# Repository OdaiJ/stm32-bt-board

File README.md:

# STM32 Bluetooth Demo Board

## Overview

A demo board I made as a project to learn PCB design fundamentals. The board is missing
some key features that make it general purpose; like headers for the unused MCU pins, however, it was a fun little project that took me a few months :)

This board was designed according to Phil's Lab's amazing videos on YouTube.

Click here to view it on 

## Todos

1. More careful choice of components for BOM; as the MOQ is too high for most components as of now.

## Notes

Assembly PDFs are broken - KiCad won't export them correctly for some reason.

Also, as of now, I had to manually edit the CPL file so JLCPCB doesn't cry about it. P.S.: I do NOT recommend using the the JLCPCB Fabrication Tool KiCad plugin; because it didn't work for me - but that was probably my fault though.

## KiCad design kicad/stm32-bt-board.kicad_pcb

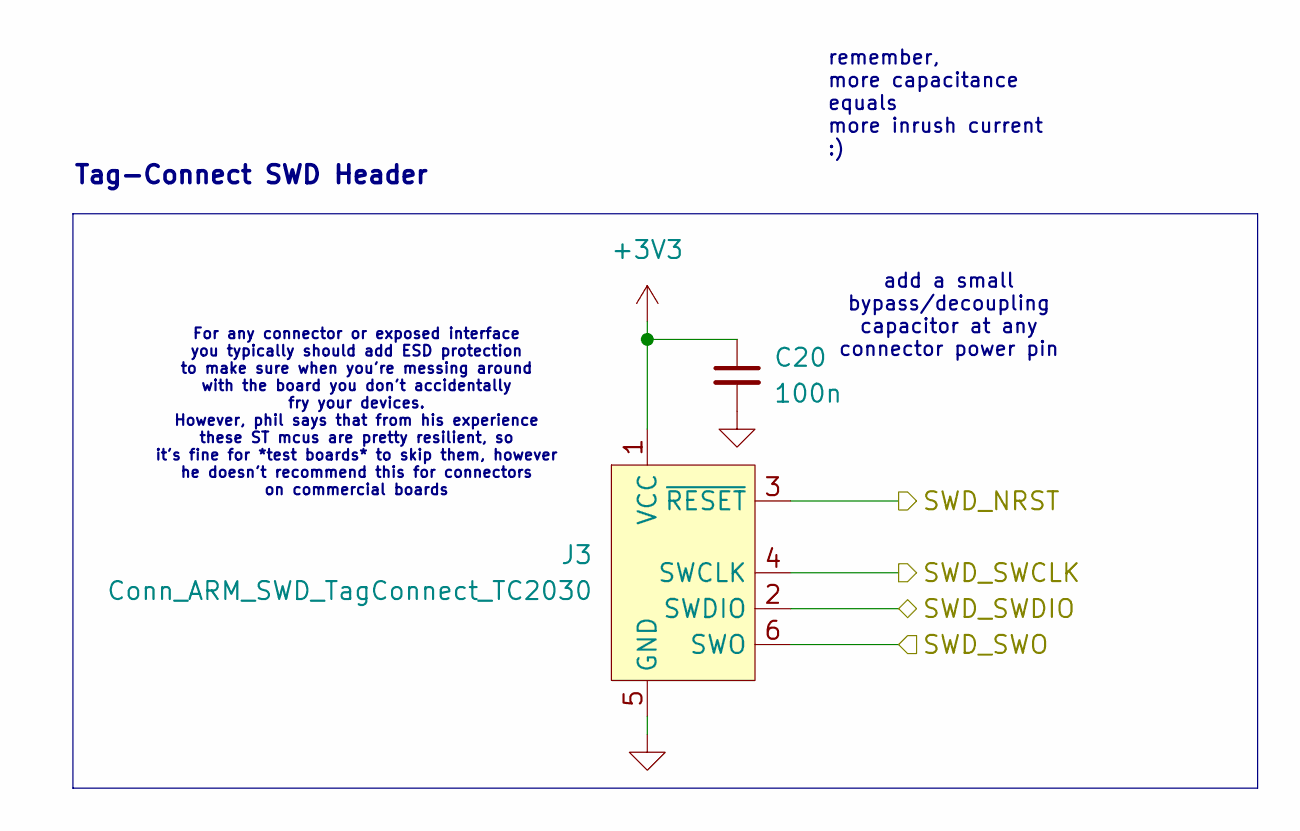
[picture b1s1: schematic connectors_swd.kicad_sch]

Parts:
C20: 100n; C_0402_1005Metric; MPN CC0402KRX7R7BB104
J3: Conn_ARM_SWD_TagConnect_TC2030; Tag-Connect_TC2030-IDC-FP_2x03_P1.27mm_Vertical

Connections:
+3V3: C20.1, J3.1 (VCC); also elsewhere on the board
/SWD_SWCLK: J3.4 (SWCLK); also elsewhere on the board
/SWD_SWDIO: J3.2 (SWDIO); also elsewhere on the board
/SWD_SWO: J3.6 (SWO); also elsewhere on the board
GND: C20.2, J3.5 (GND); also elsewhere on the board
NRST_IN: J3.3 (~RESET); also elsewhere on the board

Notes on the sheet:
remember, more capacitance equals more inrush current :)
For any connector or exposed interface you typically should add ESD protection to make sure when you're messing around with the board you don't accidentally fry your devices. However, phil says that from his experience these ST mcus are pretty resilient, so it's fine for *test boards* to skip them,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
Tag-Connect SWD Header
add a small bypass/decoupling capacitor at any connector power pin

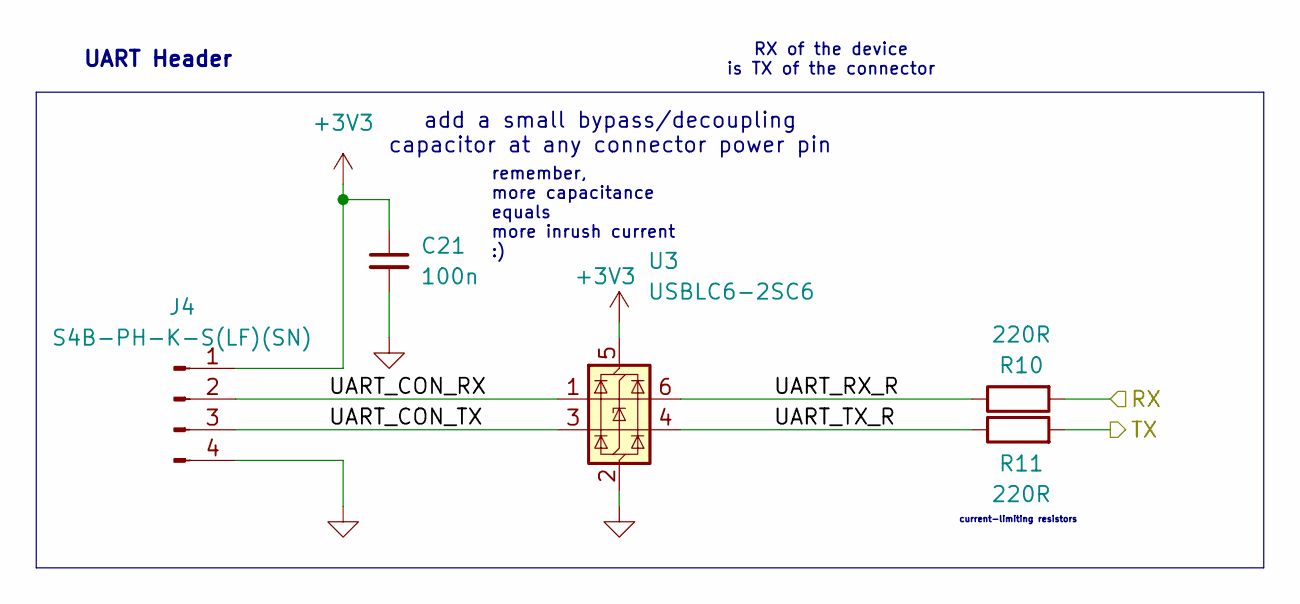
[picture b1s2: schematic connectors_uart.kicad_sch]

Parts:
C21: 100n; C_0402_1005Metric; MPN CC0402KRX7R7BB104
J4: S4B-PH-K-S(LF)(SN); MPN S4B-PH-K-S(LF)(SN)
R10, R11: 220R; R_0402_1005Metric; MPN FRC0402F2200TS
U3: USBLC6-2SC6; SOT-23-6; MPN USBLC6-2SC6

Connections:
+3V3: C21.1, J4.1, U3.5 (VBUS); also elsewhere on the board
/Connectors/UART/UART_CON_RX: J4.2, U3.1 (I/O1)
/Connectors/UART/UART_CON_TX: J4.3, U3.3 (I/O2)
/Connectors/UART/UART_RX_R: R10.1, U3.6 (I/O1)
/Connectors/UART/UART_TX_R: R11.1, U3.4 (I/O2)
/UART_MCU_RX: R11.2; also elsewhere on the board
/UART_MCU_TX: R10.2; also elsewhere on the board
GND: C21.2, J4.4, U3.2 (GND); also elsewhere on the board

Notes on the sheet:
remember, more capacitance equals more inrush current :)
add a small bypass/decoupling capacitor at any connector power pin
UART Header
RX of the device is TX of the connector
current-limiting resistors

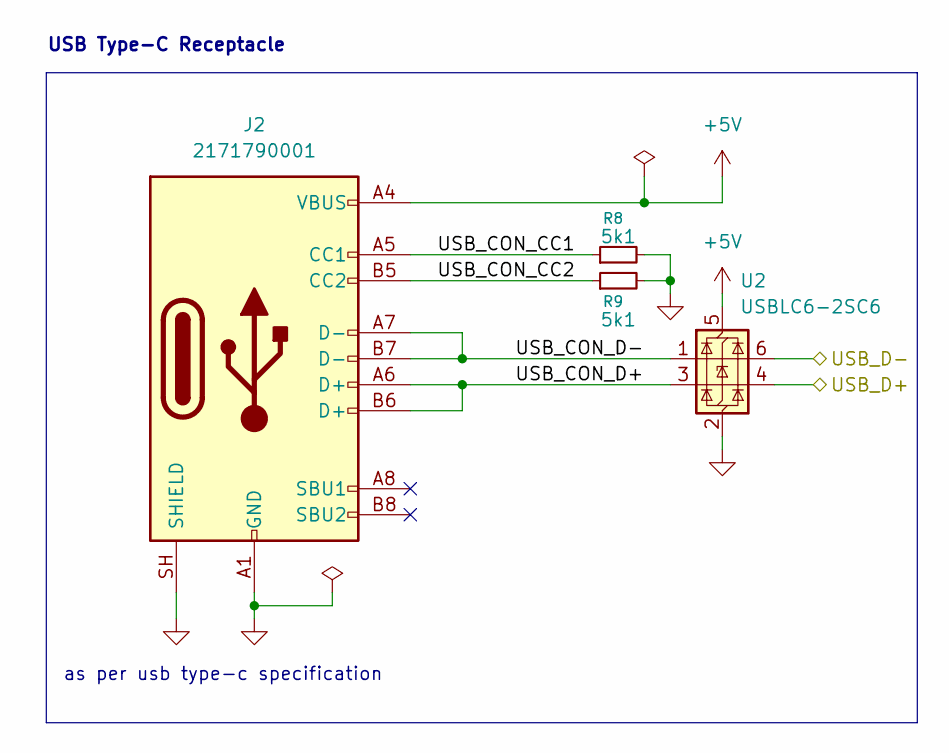
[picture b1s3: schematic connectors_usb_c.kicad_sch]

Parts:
J2: 2171790001; MPN 2171790001
R8, R9: 5k1; R_0402_1005Metric; MPN RC0402FR-075K1L
U2: USBLC6-2SC6; SOT-23-6; MPN USBLC6-2SC6

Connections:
+5V: J2.A4 (VBUS), J2.A9 (VBUS), J2.B4 (VBUS), J2.B9 (VBUS), U2.5 (VBUS); also elsewhere on the board
/Connectors/USB Type C/USB_CON_CC1: J2.A5 (CC1), R8.1
/Connectors/USB Type C/USB_CON_CC2: J2.B5 (CC2), R9.1
/Connectors/USB Type C/USB_CON_D+: J2.A6 (D+), J2.B6 (D+), U2.3 (I/O2)
/Connectors/USB Type C/USB_CON_D-: J2.A7 (D-), J2.B7 (D-), U2.1 (I/O1)
/USB_D+: U2.4 (I/O2); also elsewhere on the board
/USB_D-: U2.6 (I/O1); also elsewhere on the board
GND: J2.A1 (GND), J2.A12 (GND), J2.B1 (GND), J2.B12 (GND), J2.SH (SHIELD), R8.2, R9.2, U2.2 (GND); also elsewhere on the board

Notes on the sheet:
USB Type-C Receptacle
as per usb type-c specification

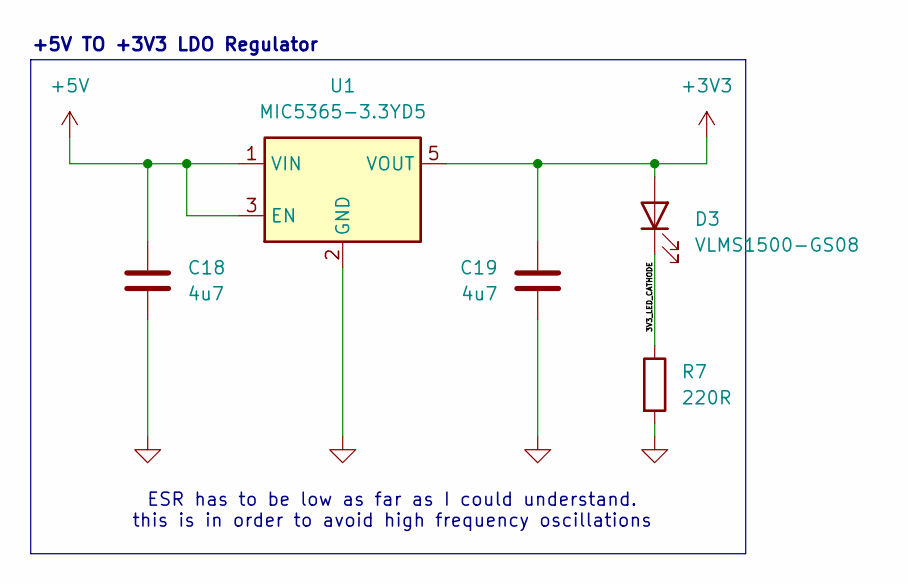
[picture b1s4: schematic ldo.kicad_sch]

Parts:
C18, C19: 4u7; C_0603_1608Metric; MPN CL10A475KL8NRNC
D3: VLMS1500-GS08; LED_0402_1005Metric; MPN VLMS1500-GS08
R7: 220R; R_0402_1005Metric; MPN FRC0402F2200TS
U1: MIC5365-3.3YD5; TSOT-23-5; MPN MIC5365-3.3YD5-TR

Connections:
+3V3: C19.1, D3.2 (A), U1.5 (VOUT); also elsewhere on the board
+5V: C18.1, U1.1 (VIN), U1.3 (EN); also elsewhere on the board
/LDO/3V3_LED_CATHODE: D3.1 (K), R7.1
GND: C18.2, C19.2, R7.2, U1.2 (GND); also elsewhere on the board

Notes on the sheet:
+5V TO +3V3 LDO Regulator
ESR has to be low as far as I could understand. this is in order to avoid high frequency oscillations

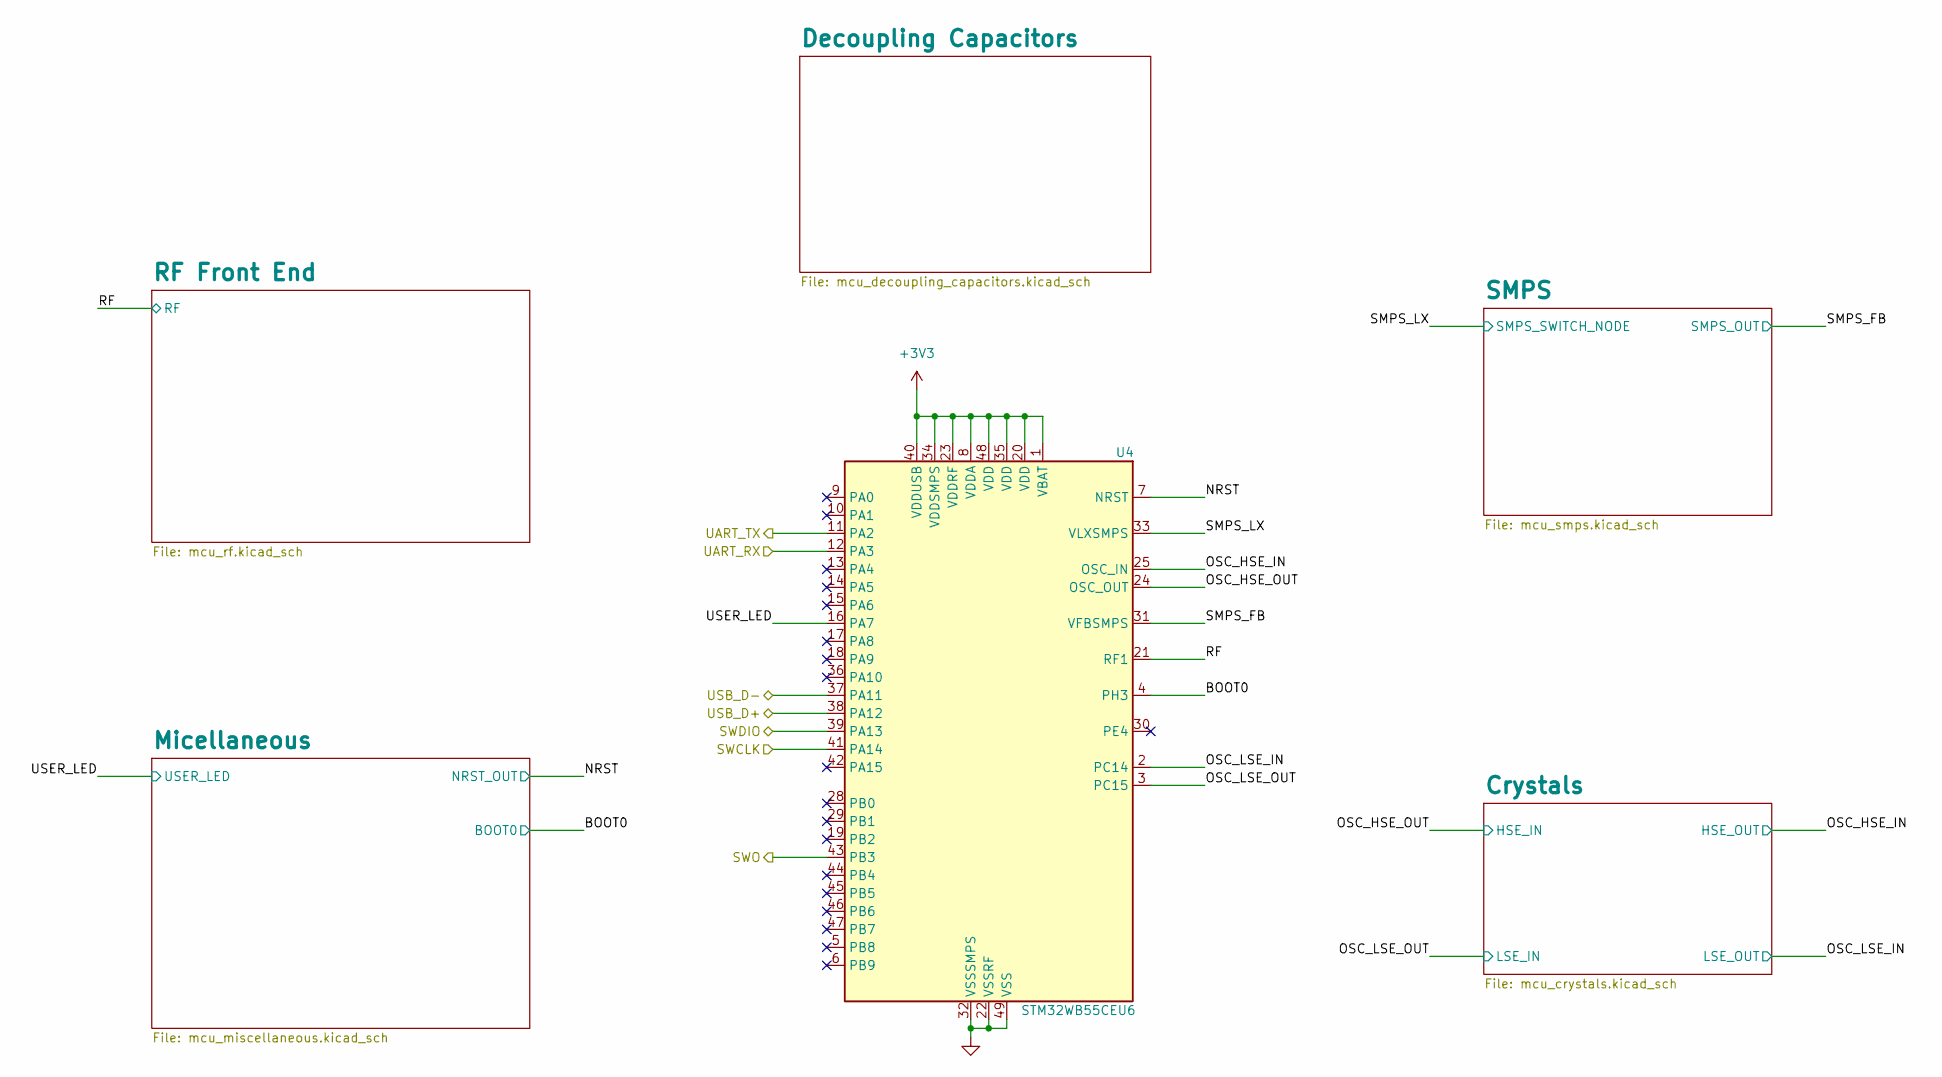
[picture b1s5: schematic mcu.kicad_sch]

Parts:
U4: STM32WB55CEU6; QFN-48-1EP_7x7mm_P0.5mm_EP5.6x5.6mm; MPN STM32WB55CEU6

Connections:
+3V3: U4.1 (VBAT), U4.8 (VDDA), U4.20 (VDD), U4.23 (VDDRF), U4.34 (VDDSMPS), U4.35 (VDD), U4.40 (VDDUSB), U4.48 (VDD); also elsewhere on the board
/Microcontroller/BOOT0: U4.4 (PH3); also elsewhere on the board
/Microcontroller/NRST: U4.7 (NRST); also elsewhere on the board
/Microcontroller/OSC_HSE_IN: U4.25 (OSC_IN); also elsewhere on the board
/Microcontroller/OSC_HSE_OUT: U4.24 (OSC_OUT); also elsewhere on the board
/Microcontroller/OSC_LSE_IN: U4.2 (PC14); also elsewhere on the board
/Microcontroller/OSC_LSE_OUT: U4.3 (PC15); also elsewhere on the board
/Microcontroller/RF: U4.21 (RF1); also elsewhere on the board
/Microcontroller/SMPS_FB: U4.31 (VFBSMPS); also elsewhere on the board
/Microcontroller/SMPS_LX: U4.33 (VLXSMPS); also elsewhere on the board
/Microcontroller/USER_LED: U4.16 (PA7); also elsewhere on the board
/SWD_SWCLK: U4.41 (PA14); also elsewhere on the board
/SWD_SWDIO: U4.39 (PA13); also elsewhere on the board
/SWD_SWO: U4.43 (PB3); also elsewhere on the board
/UART_MCU_RX: U4.12 (PA3); also elsewhere on the board
/UART_MCU_TX: U4.11 (PA2); also elsewhere on the board
/USB_D+: U4.38 (PA12); also elsewhere on the board
/USB_D-: U4.37 (PA11); also elsewhere on the board
GND: U4.22 (VSSRF), U4.32 (VSSSMPS), U4.49 (VSS); also elsewhere on the board

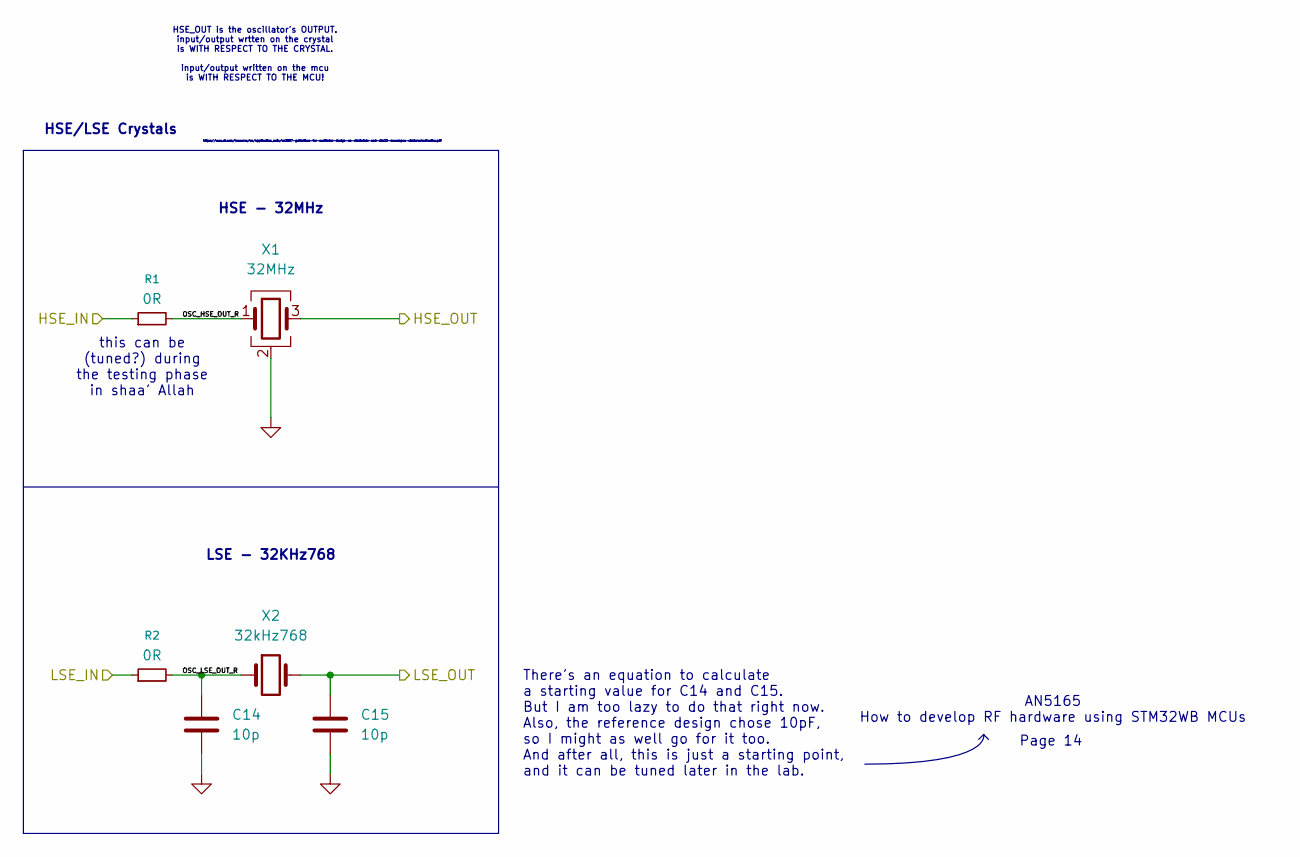
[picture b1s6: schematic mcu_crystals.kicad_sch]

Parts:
C14, C15: 10p; C_0402_1005Metric; MPN GRM1555C1H100FA01D
R1, R2: 0R; R_0402_1005Metric; MPN CRCW04020000Z0ED
X1: 32MHz; Crystal_SMD_2016-4Pin_2.0x1.6mm; MPN NX2016SA-32MHZ-EXS00A-CS06654
X2: 32kHz768; Crystal_SMD_2012-2Pin_2.0x1.2mm; MPN NX2012SA-32.768KHZ-STD-MUB-2

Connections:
/Microcontroller/Crystals/OSC_HSE_OUT_R: R1.2, X1.1
/Microcontroller/Crystals/OSC_LSE_OUT_R: C14.1, R2.2, X2.1
/Microcontroller/OSC_HSE_IN: X1.3; also elsewhere on the board
/Microcontroller/OSC_HSE_OUT: R1.1; also elsewhere on the board
/Microcontroller/OSC_LSE_IN: C15.1, X2.2; also elsewhere on the board
/Microcontroller/OSC_LSE_OUT: R2.1; also elsewhere on the board
GND: C14.2, C15.2, X1.2 (G), X1.4 (G); also elsewhere on the board

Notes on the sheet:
HSE/LSE Crystals
HSE - 32MHz
https://www.st.com/resource/en/application_note/an2867-guidelines-for-oscillator-design-on-stm8afals-and-stm32-mcusmpus-stmicroelectronics.pdf
LSE - 32KHz768
Page 14
AN5165 How to develop RF hardware using STM32WB MCUs
There's an equation to calculate a starting value for C14 and C15. But I am too lazy to do that right now. Also, the reference design chose 10pF, so I might as well go for it too. And after all, this is just a starting point, and it can be tuned later in the lab.
this can be (tuned?) during the testing phase in shaa' Allah
HSE_OUT is the oscillator's OUTPUT. input/output wrtten on the crystal is WITH RESPECT TO THE CRYSTAL. input/output written on the mcu is WITH RESPECT TO THE MCU!

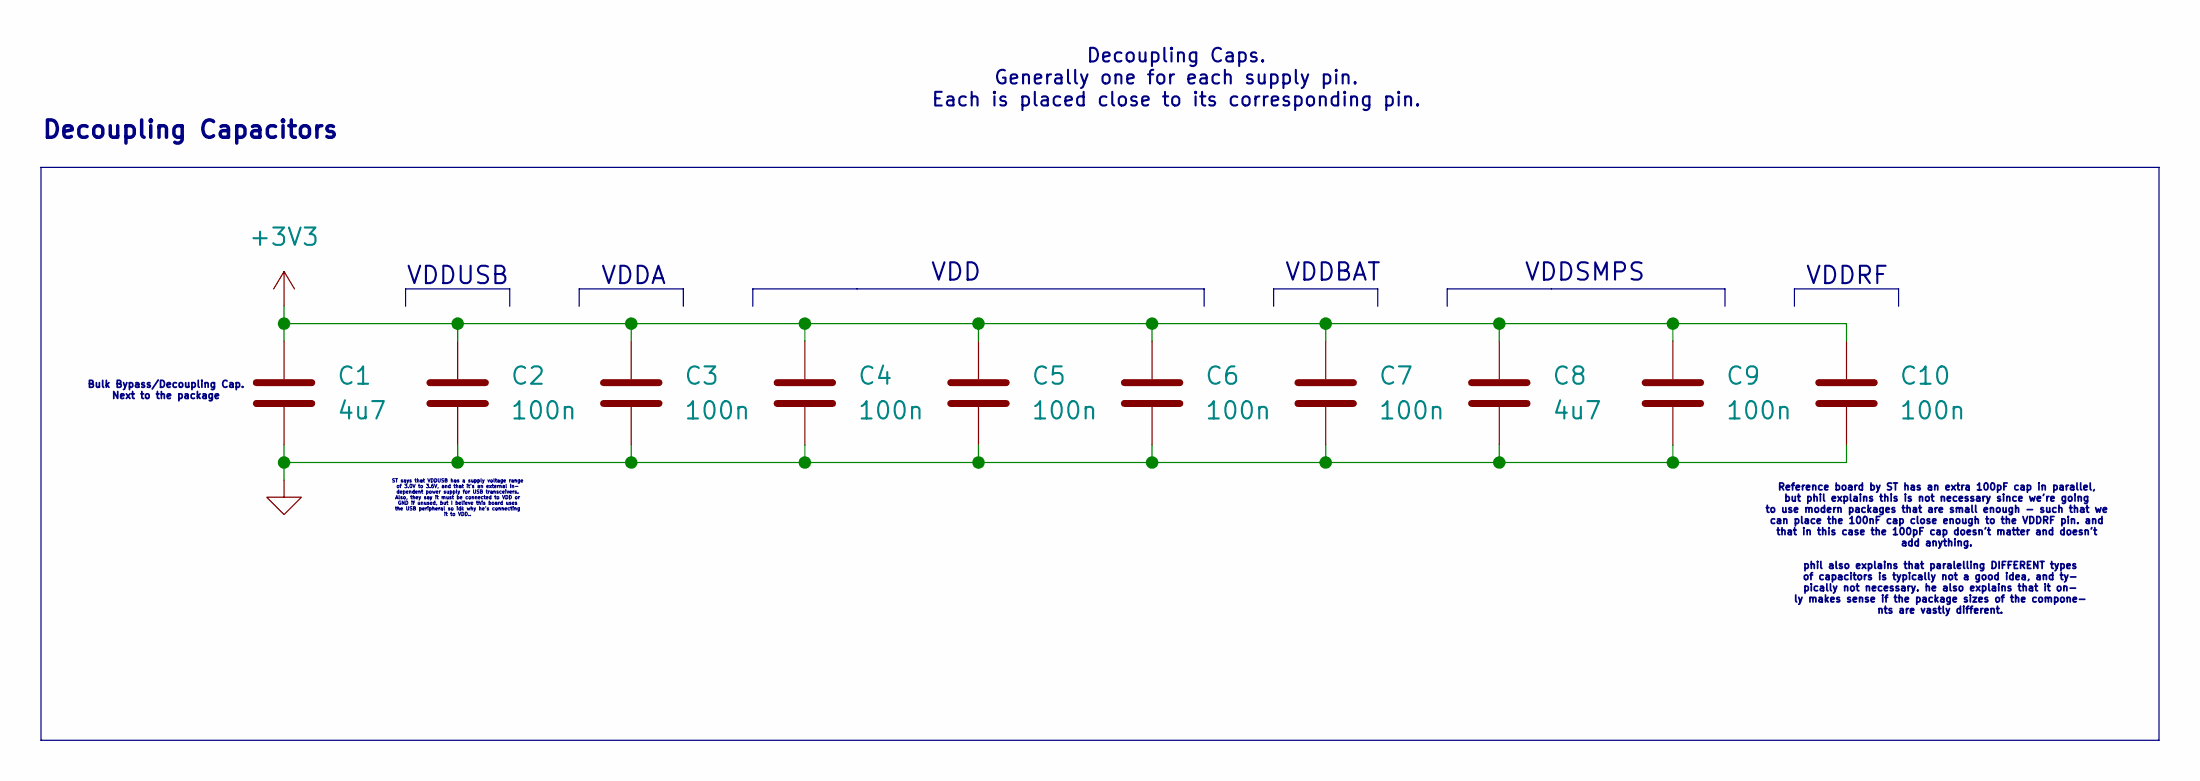
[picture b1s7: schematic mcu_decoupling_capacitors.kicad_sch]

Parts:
C1, C8: 4u7; C_0603_1608Metric; MPN CL10A475KL8NRNC
C2, C3, C4, C5, C6, C7, C9, C10: 100n; C_0402_1005Metric; MPN CC0402KRX7R7BB104

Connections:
+3V3: C1.1, C2.1, C3.1, C4.1, C5.1, C6.1, C7.1, C8.1, C9.1, C10.1; also elsewhere on the board
GND: C1.2, C2.2, C3.2, C4.2, C5.2, C6.2, C7.2, C8.2, C9.2, C10.2; also elsewhere on the board

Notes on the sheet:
VDDRF
VDD
Decoupling Caps. Generally one for each supply pin. Each is placed close to its corresponding pin.
Reference board by ST has an extra 100pF cap in parallel, but phil explains this is not necessary since we're going to use modern packages that are small enough - such that we can place the 100nF cap close enough to the VDDRF pin. and that in this case the 100pF cap doesn't matter and doesn't add a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
phil also explains that paralelling DIFFERENT types of capacitors is typically not a good idea, and ty- pically not necessary. he also explains that it on- ly makes sense if the package sizes of the compone- nts are vastly different.
Bulk Bypass/Decoupling Cap. Next to the package
Decoupling Capacitors
VDDBAT
VDDUSB
VDDA
ST says that VDDUSB has a supply voltage range of 3.0V to 3.6V, and that it's an external in- dependent power supply for USB transceivers. Also, they say it must be connected to VDD or GND if unused, but I believe this board uses the USB peripheral so idk why he's connecting it to VDD..
VDDSMPS

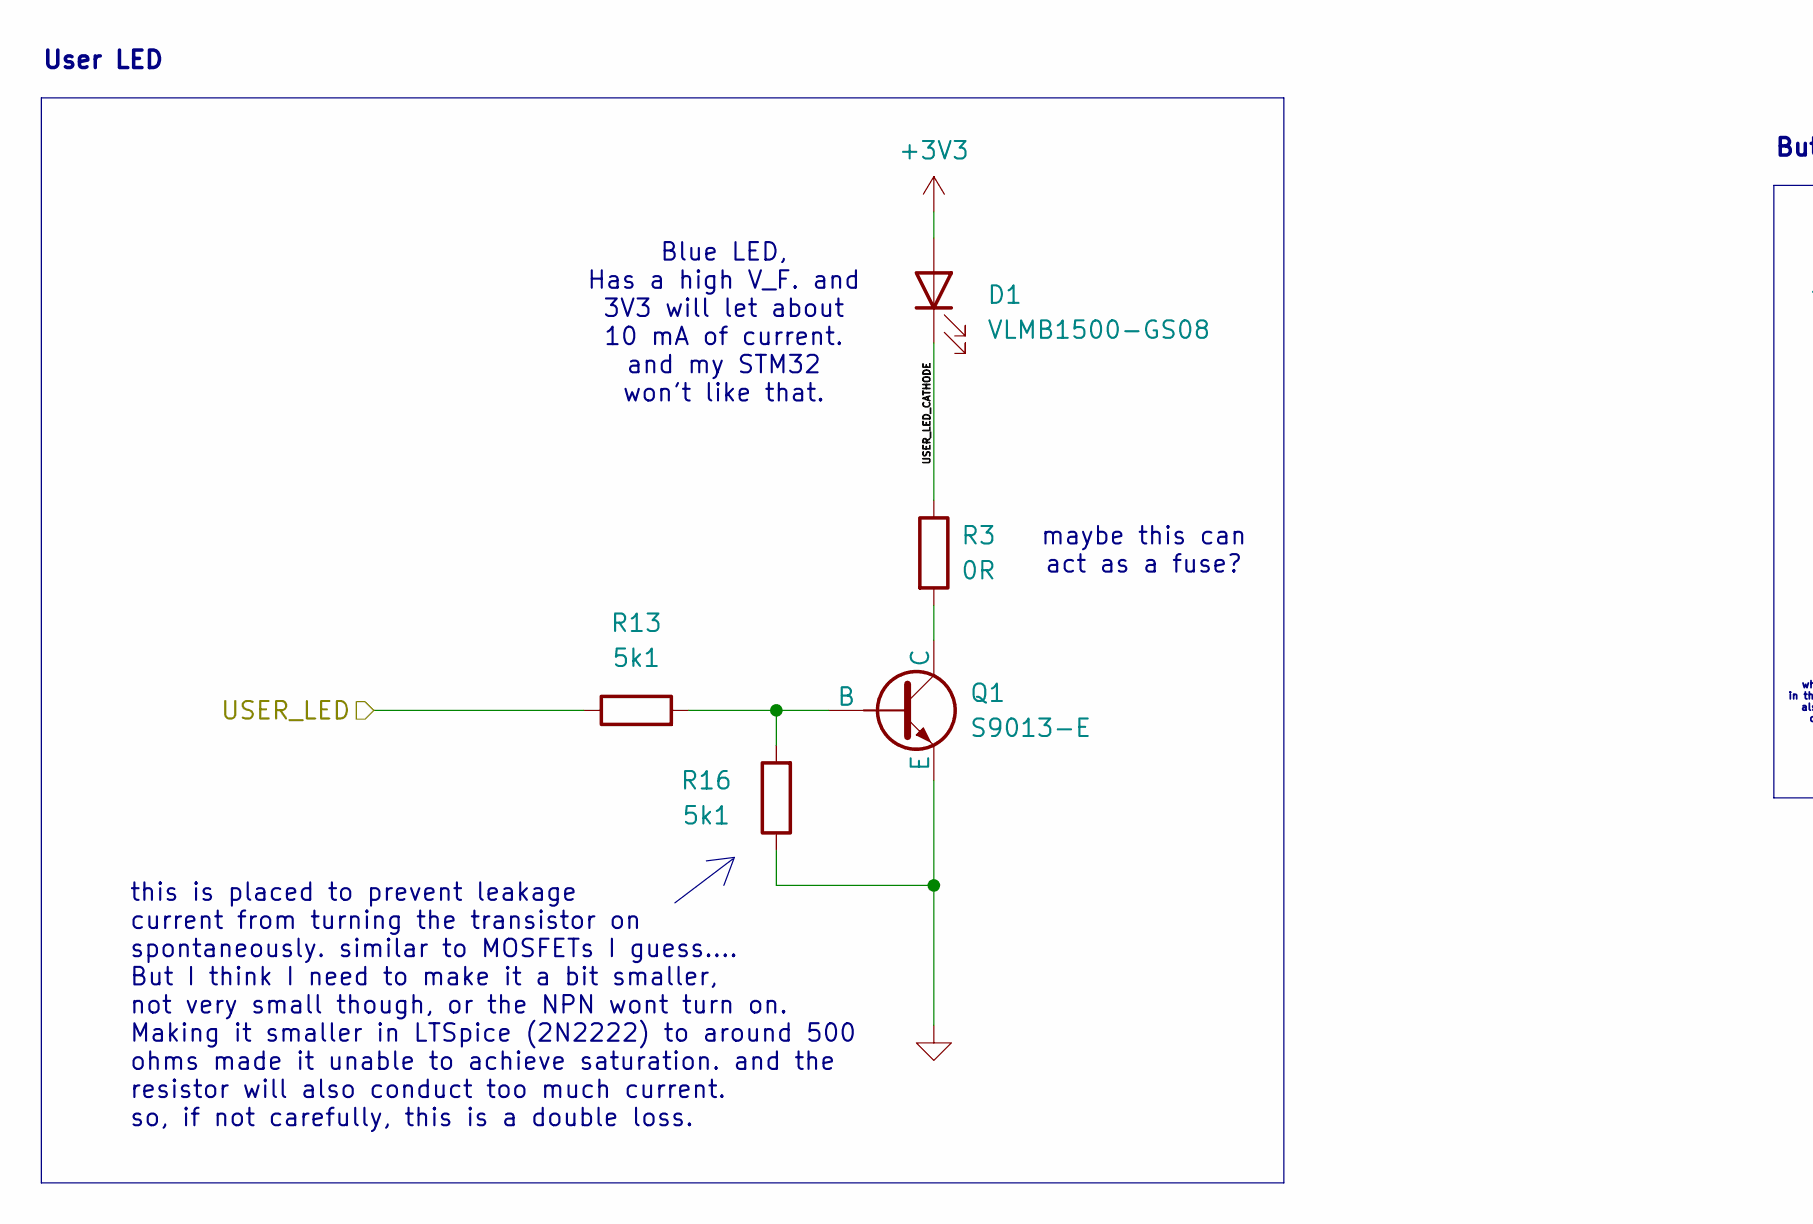
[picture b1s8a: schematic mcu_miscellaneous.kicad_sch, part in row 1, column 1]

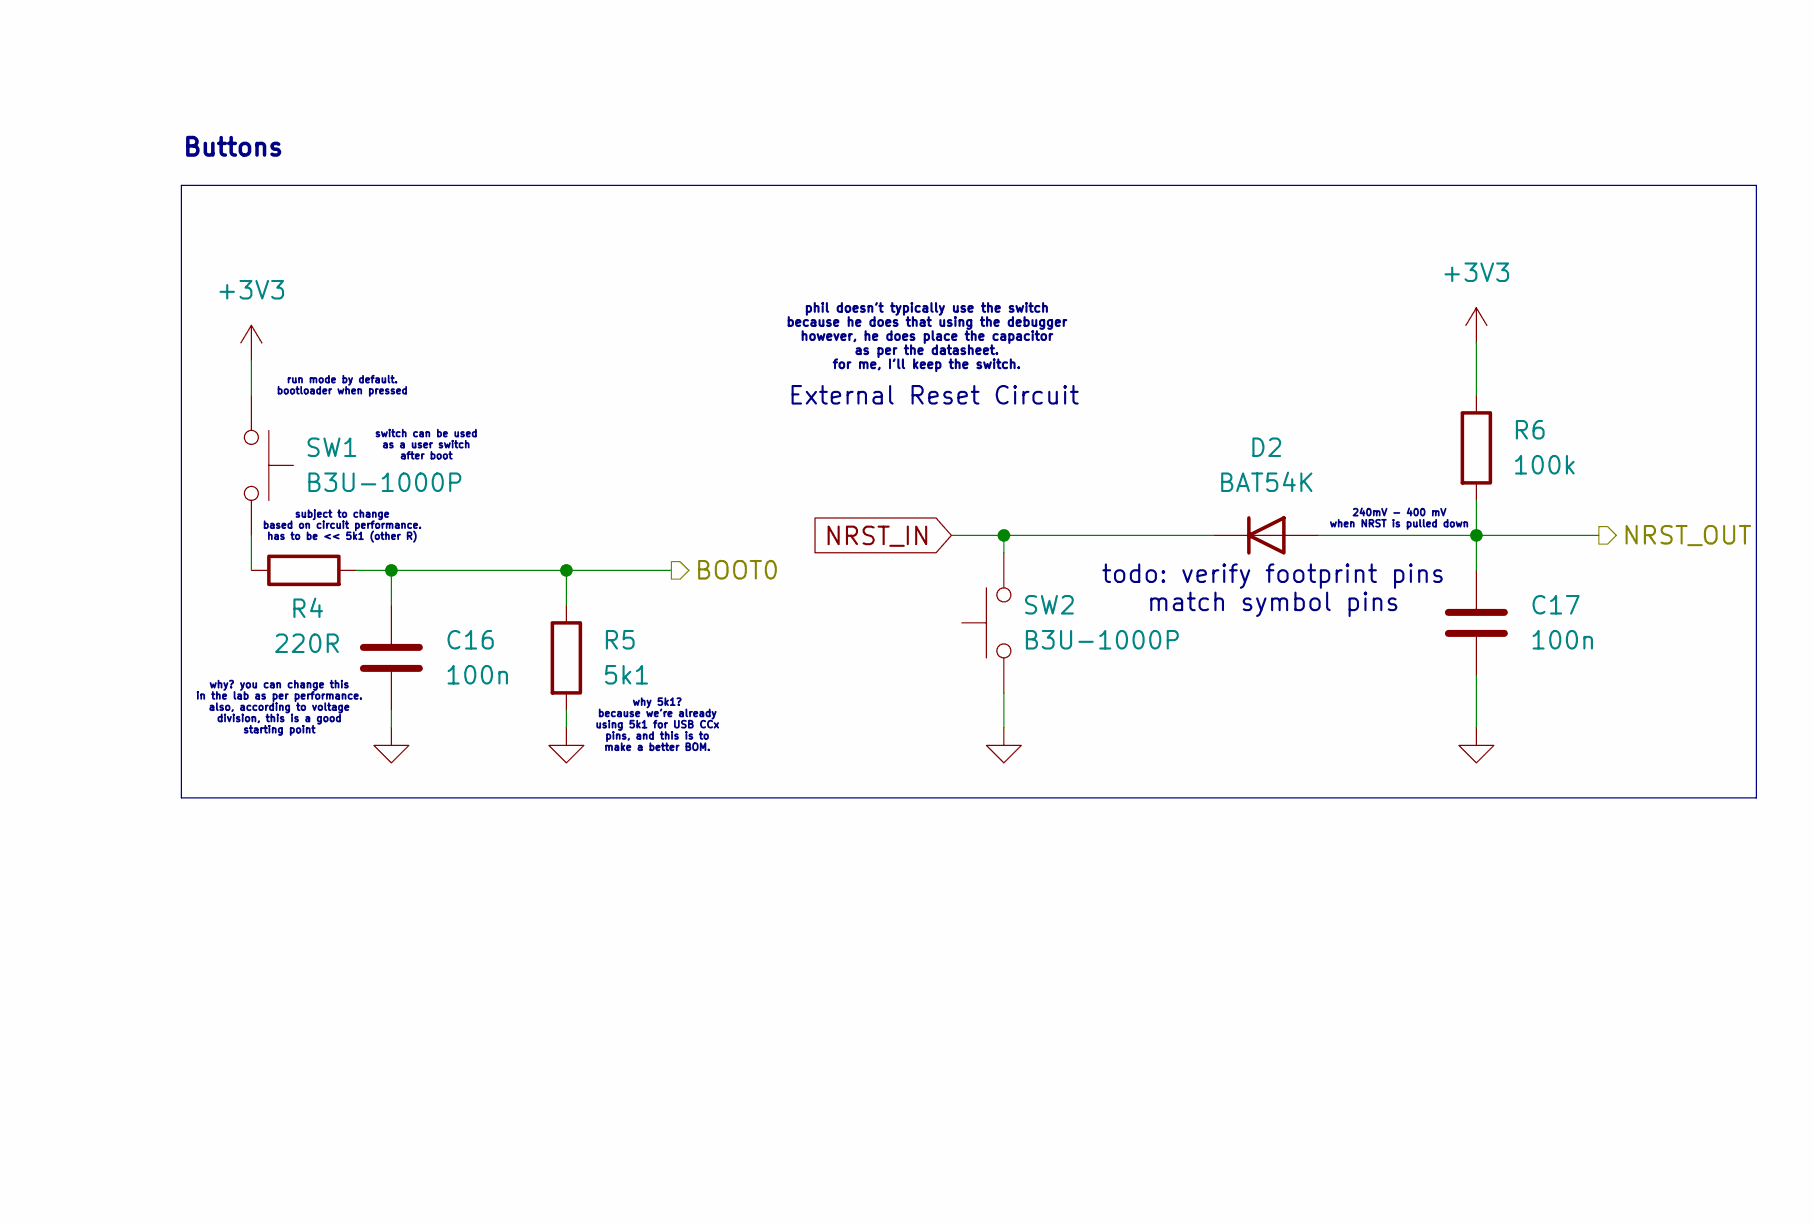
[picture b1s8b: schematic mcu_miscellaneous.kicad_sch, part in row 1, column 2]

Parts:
C16, C17: 100n; C_0402_1005Metric; MPN CC0402KRX7R7BB104
D1: VLMB1500-GS08; LED_0402_1005Metric; MPN VLMB1500-GS08
D2: BAT54K; D_SOD-523; MPN BAT54KFILM
Q1: S9013-E; SOT-23; MPN S9013-E
R3: 0R; R_0402_1005Metric; MPN CRCW04020000Z0ED
R4: 220R; R_0402_1005Metric; MPN FRC0402F2200TS
R5, R13, R16: 5k1; R_0402_1005Metric; MPN RC0402FR-075K1L
R6: 100k; R_0402_1005Metric; MPN RC0402FR-07100KL
SW1, SW2: B3U-1000P; MPN B3U-1000P

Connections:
+3V3: D1.2 (A), R6.1, SW1.1; also elsewhere on the board
/Microcontroller/BOOT0: C16.1, R4.2, R5.1; also elsewhere on the board
/Microcontroller/Micellaneous/USER_LED_CATHODE: D1.1 (K), R3.1
/Microcontroller/NRST: C17.1, D2.2 (A), R6.2; also elsewhere on the board
/Microcontroller/USER_LED: R13.1; also elsewhere on the board
GND: C16.2, C17.2, Q1.2 (E), R5.2, R16.1, SW2.1; also elsewhere on the board
NRST_IN: D2.1 (K), SW2.2; also elsewhere on the board
unnamed: Q1.1 (B), R13.2, R16.2
unnamed: Q1.3 (C), R3.2
unnamed: R4.1, SW1.2

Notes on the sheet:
Buttons
External Reset Circuit
phil doesn't typically use the switch because he does that using the debugger however, he does place the capacitor as per the datasheet. for me, I'll keep the switch.
todo: verify footprint pins match symbol pins
Blue LED, Has a high V_F. and 3V3 will let about 10 mA of current. and my STM32 won't like that.
run mode by default. bootloader when pressed
240mV - 400 mV when NRST is pulled down
maybe this can act as a fuse?
why? you can change this in the lab as per performance. also, according to voltage division, this is a good starting point
why 5k1? because we're already using 5k1 for USB CCx pins, and this is to make a better BOM.
this is placed to prevent leakage current from turning the transistor on spontaneously. similar to MOSFETs I guess.... But I think I need to make it a bit smaller, not very small though, or the NPN wont turn on. Making it smaller in LTSpice (2N2222) to around 500 ohms made it unable to achieve satu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
subject to change based on circuit performance. has to be << 5k1 (other R)
switch can be used as a user switch after boot
User LED

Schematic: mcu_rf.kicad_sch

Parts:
C12: 0p8; C_0402_1005Metric; MPN GRM1555C1HR80BA01D
C13: 0p3; C_0402_1005Metric; MPN GRM1555C1HR30WA01D
FL1: DLF162500LT-5028A1; MPN DLF162500LT-5028A1
J1: 1909763-1; MPN 1909763-1
L3: 2n7; L_0402_1005Metric; MPN LQG15HS2N7S02D

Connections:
/Microcontroller/RF: C12.1, L3.1; also elsewhere on the board
/Microcontroller/RF Front End/RF_ANT: FL1.3 (OUT), J1.1 (In)
/Microcontroller/RF Front End/RF_MATCH: C13.1, FL1.1 (IN), L3.2
GND: C12.2, C13.2, FL1.2 (GND), FL1.4 (GND), J1.2 (Ext), J1.3 (Ext); also elsewhere on the board

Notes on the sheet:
50 Ohms Matching Network
RF Front-End
layout: careful layout needed? answer: yes

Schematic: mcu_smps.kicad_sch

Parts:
C11: 4u7; C_0603_1608Metric; MPN CL10A475KL8NRNC
L1: 10n; L_0402_1005Metric; MPN LQG15WZ10NJ02D
L2: 10u; L_0805_2012Metric; MPN LQM21FN100M80L

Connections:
/Microcontroller/SMPS/SMPS_LXL: L1.2, L2.1
/Microcontroller/SMPS_FB: C11.1, L2.2; also elsewhere on the board
/Microcontroller/SMPS_LX: L1.1; also elsewhere on the board
GND: C11.2; also elsewhere on the board

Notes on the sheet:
SMPS
AN5246 How to use SMPS to improve power efficiency on STM32WB MCUs
